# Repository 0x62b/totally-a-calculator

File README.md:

# totally a calculator
This is a RPi Pico powered...calculator...with an extensive library of..."extra apps" one could say.
The sole purpose of this project is to satisfy the ask of one of my classmates :sob:

[Onshape link](https://cad.onshape.com/documents/416f156d5c7fec03dfea0d3a/w/a37f3b67ee07a3cc1823a5f4/e/b4b6719643a130719caaa4b0)
Note: the display appears to be unaligned due to the fact that i used a different display to the model in the render. However, I designed the case around the display being used, so it should be fine.

## Repo structure
`firmware/` for the (not completed) firmware
`cad/` for CAD design files
`images/` for images in this readme
`pcb/` for KiCad design files and `pcb/gerbers` for production files
`bom.csv` for BOM

## Cost
The BOM prices are approximate due to conversion rates and Aliexpress fluctuations
BOM: 27.03 USD
PCB: 4 USD + 1.5 USD shipping (approx)
Total: 32.53 USD

## Assembly
Prerequisites: print the case parts and solder the PCB
1. Put PCB into bottom case
2. Screw top case onto bottom case
3. Glue or otherwise stick each individual keycap onto the buttons
4. Attach the OLED
5. Screw it in
6. Flash the MicroPython firmware for the Pico
7. Upload the python file in `firmware/`
8. yay

## Images

### Schematic
Beautifully clean and organised (/s) schematic

### PCB render

### Full render

### Zine

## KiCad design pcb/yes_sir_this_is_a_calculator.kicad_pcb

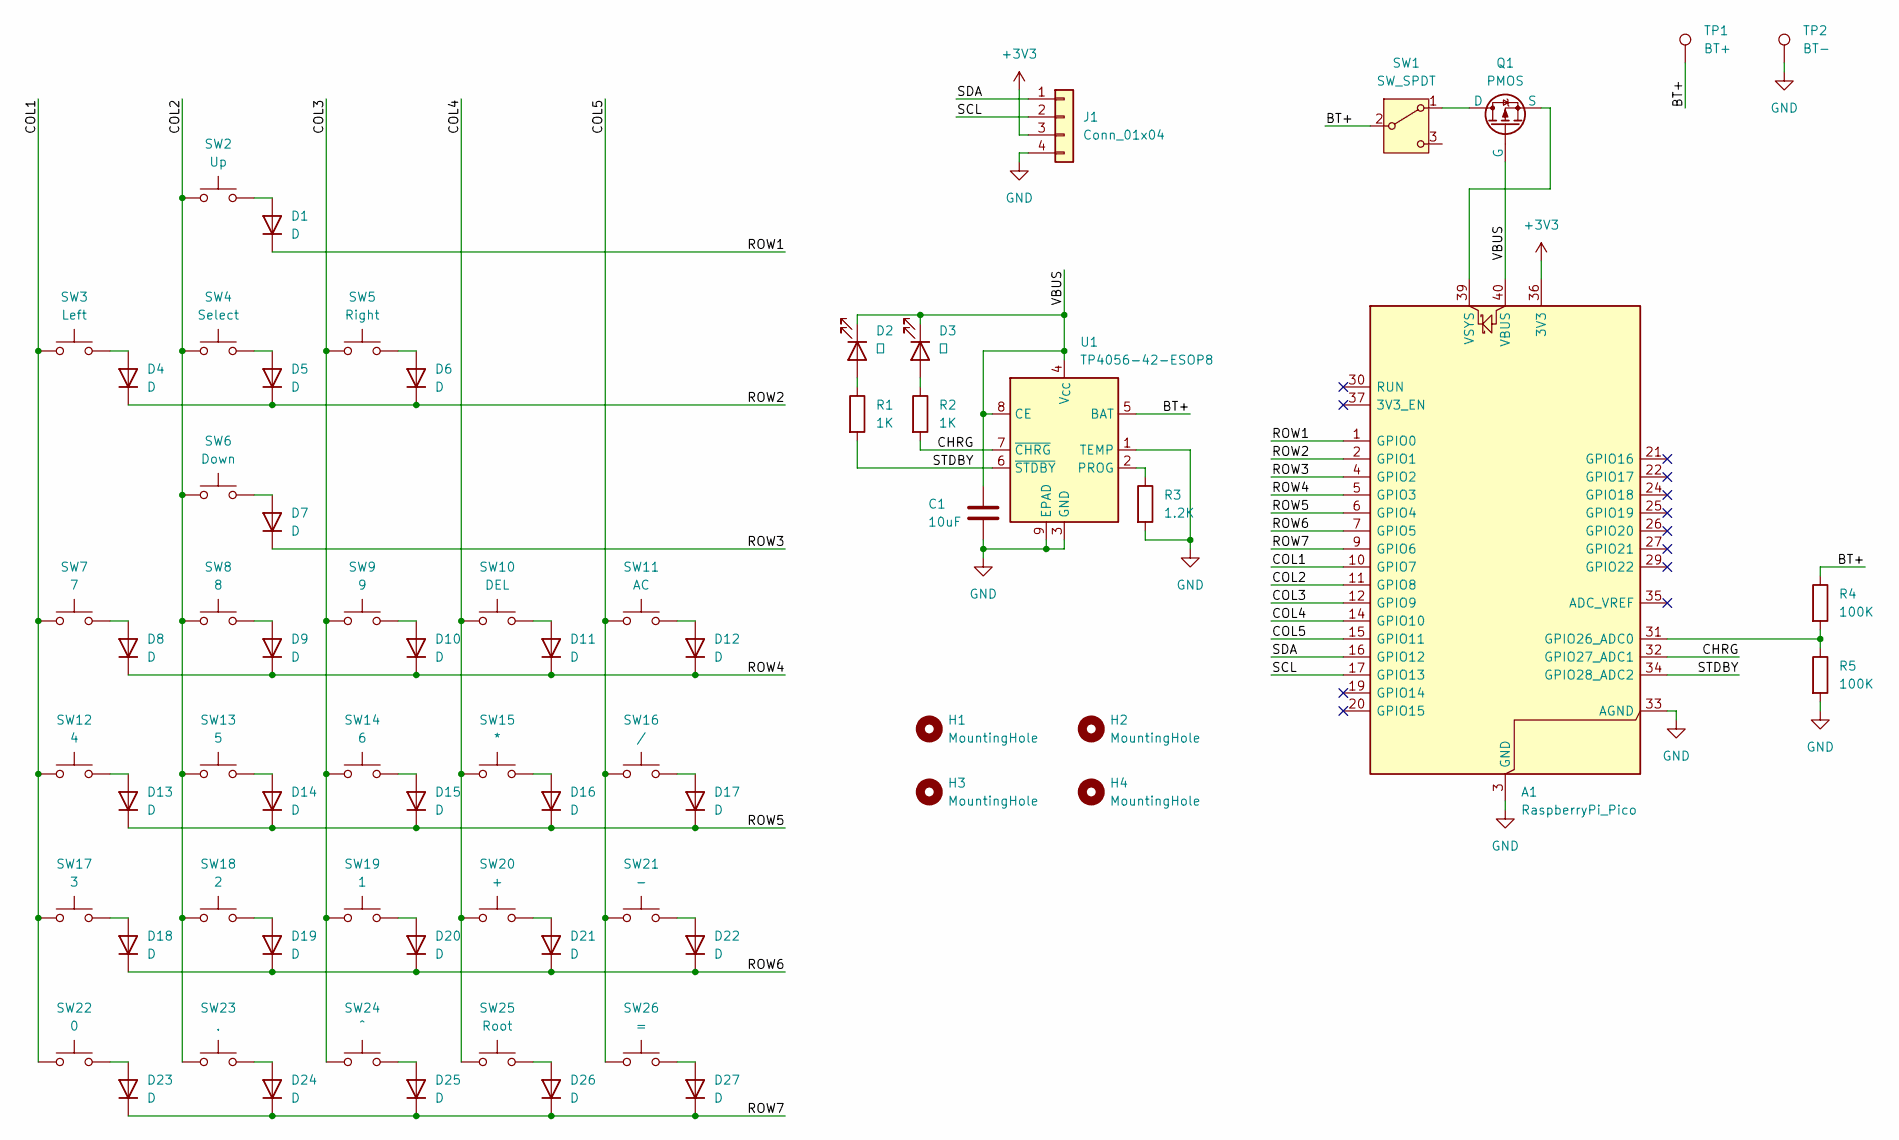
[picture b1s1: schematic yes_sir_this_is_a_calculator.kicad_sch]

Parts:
A1: RaspberryPi_Pico; RaspberryPi_Pico_Common_Unspecified
C1: 10uF; C_0402_1005Metric
D1, D4, D5, D6, D7, D8, D9, D10, D11, D12, D13, D14, D15, D16, D17, D18, D19, D20, D21, D22, D23, D24, D25, D26, D27: D; D_SOD-123
D2: 绿; LED_0402_1005Metric
D3: 红; LED_0402_1005Metric
H1, H2, H3, H4: MountingHole; MountingHole_2.2mm_M2
J1: Conn_01x04; PinSocket_1x04_P2.54mm_Vertical
Q1: PMOS; SOT-23
R1, R2: 1K; R_0402_1005Metric
R3: 1.2K; R_0402_1005Metric
R4, R5: 100K; R_0402_1005Metric
SW1: SW_SPDT; SW_SPDT_PCM12
SW2: Up; SW_PUSH_6mm
SW3: Left; SW_PUSH_6mm
SW4: Select; SW_PUSH_6mm
SW5: Right; SW_PUSH_6mm
SW6: Down; SW_PUSH_6mm
SW7: 7; SW_PUSH_6mm
SW8: 8; SW_PUSH_6mm
SW9: 9; SW_PUSH_6mm
SW10: DEL; SW_PUSH_6mm
SW11: AC; SW_PUSH_6mm
SW12: 4; SW_PUSH_6mm
SW13: 5; SW_PUSH_6mm
SW14: 6; SW_PUSH_6mm
SW15: *; SW_PUSH_6mm
SW16: /; SW_PUSH_6mm
SW17: 3; SW_PUSH_6mm
SW18: 2; SW_PUSH_6mm
SW19: 1; SW_PUSH_6mm
SW20: +; SW_PUSH_6mm
SW21: -; SW_PUSH_6mm
SW22: 0; SW_PUSH_6mm
SW23: .; SW_PUSH_6mm
SW24: ^; SW_PUSH_6mm
SW25: Root; SW_PUSH_6mm
SW26: =; SW_PUSH_6mm
TP1: BT+; TestPoint_Pad_D3.0mm
TP2: BT-; TestPoint_Pad_D3.0mm
U1: TP4056-42-ESOP8; SOIC-8-1EP_3.9x4.9mm_P1.27mm_EP2.41x3.3mm_ThermalVias

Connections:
+3V3: A1.36 (3V3), J1.3
/BT+: R4.1, SW1.2 (B), TP1.1, U1.5 (BAT)
/CHRG: A1.32 (GPIO27_ADC1), R2.2, U1.7 (~CHRG)
/COL1: A1.10 (GPIO7), SW3.1, SW7.1, SW12.1, SW17.1, SW22.1
/COL2: A1.11 (GPIO8), SW2.1, SW4.1, SW6.1, SW8.1, SW13.1, SW18.1, SW23.1
/COL3: A1.12 (GPIO9), SW5.1, SW9.1, SW14.1, SW19.1, SW24.1
/COL4: A1.14 (GPIO10), SW10.1, SW15.1, SW20.1, SW25.1
/COL5: A1.15 (GPIO11), SW11.1, SW16.1, SW21.1, SW26.1
/ROW1: A1.1 (GPIO0), D1.1 (K)
/ROW2: A1.2 (GPIO1), D4.1 (K), D5.1 (K), D6.1 (K)
/ROW3: A1.4 (GPIO2), D7.1 (K)
/ROW4: A1.5 (GPIO3), D8.1 (K), D9.1 (K), D10.1 (K), D11.1 (K), D12.1 (K)
/ROW5: A1.6 (GPIO4), D13.1 (K), D14.1 (K), D15.1 (K), D16.1 (K), D17.1 (K)
/ROW6: A1.7 (GPIO5), D18.1 (K), D19.1 (K), D20.1 (K), D21.1 (K), D22.1 (K)
/ROW7: A1.9 (GPIO6), D23.1 (K), D24.1 (K), D25.1 (K), D26.1 (K), D27.1 (K)
/SCL: A1.17 (GPIO13), J1.2
/SDA: A1.16 (GPIO12), J1.1
/STDBY: A1.34 (GPIO28_ADC2), R1.2, U1.6 (~STDBY)
/VBUS: A1.40 (VBUS), C1.2, D2.1 (K), D3.1 (K), Q1.2 (G), U1.4 (V_{CC}), U1.8 (CE)
GND: A1.3 (GND), A1.8 (GND), A1.13 (GND), A1.18 (GND), A1.23 (GND), A1.28 (GND), A1.33 (AGND), A1.38 (GND), C1.1, J1.4, R3.2, R5.2, TP2.1, U1.1 (TEMP), U1.3 (GND), U1.9 (EPAD)
unnamed: A1.31 (GPIO26_ADC0), R4.2, R5.1
unnamed: A1.39 (VSYS), Q1.3 (S)
unnamed: D1.2 (A), SW2.2
unnamed: D2.2 (A), R1.1
unnamed: D3.2 (A), R2.1
unnamed: D4.2 (A), SW3.2
unnamed: D5.2 (A), SW4.2
unnamed: D6.2 (A), SW5.2
unnamed: D7.2 (A), SW6.2
unnamed: D8.2 (A), SW7.2
unnamed: D9.2 (A), SW8.2
unnamed: D10.2 (A), SW9.2
unnamed: D11.2 (A), SW10.2
unnamed: D12.2 (A), SW11.2
unnamed: D13.2 (A), SW12.2
unnamed: D14.2 (A), SW13.2
unnamed: D15.2 (A), SW14.2
unnamed: D16.2 (A), SW15.2
unnamed: D17.2 (A), SW16.2
unnamed: D18.2 (A), SW17.2
unnamed: D19.2 (A), SW18.2
unnamed: D20.2 (A), SW19.2
unnamed: D21.2 (A), SW20.2
unnamed: D22.2 (A), SW21.2
unnamed: D23.2 (A), SW22.2
unnamed: D24.2 (A), SW23.2
unnamed: D25.2 (A), SW24.2
unnamed: D26.2 (A), SW25.2
unnamed: D27.2 (A), SW26.2
unnamed: Q1.1 (D), SW1.1 (A)
unnamed: R3.1, U1.2 (PROG)

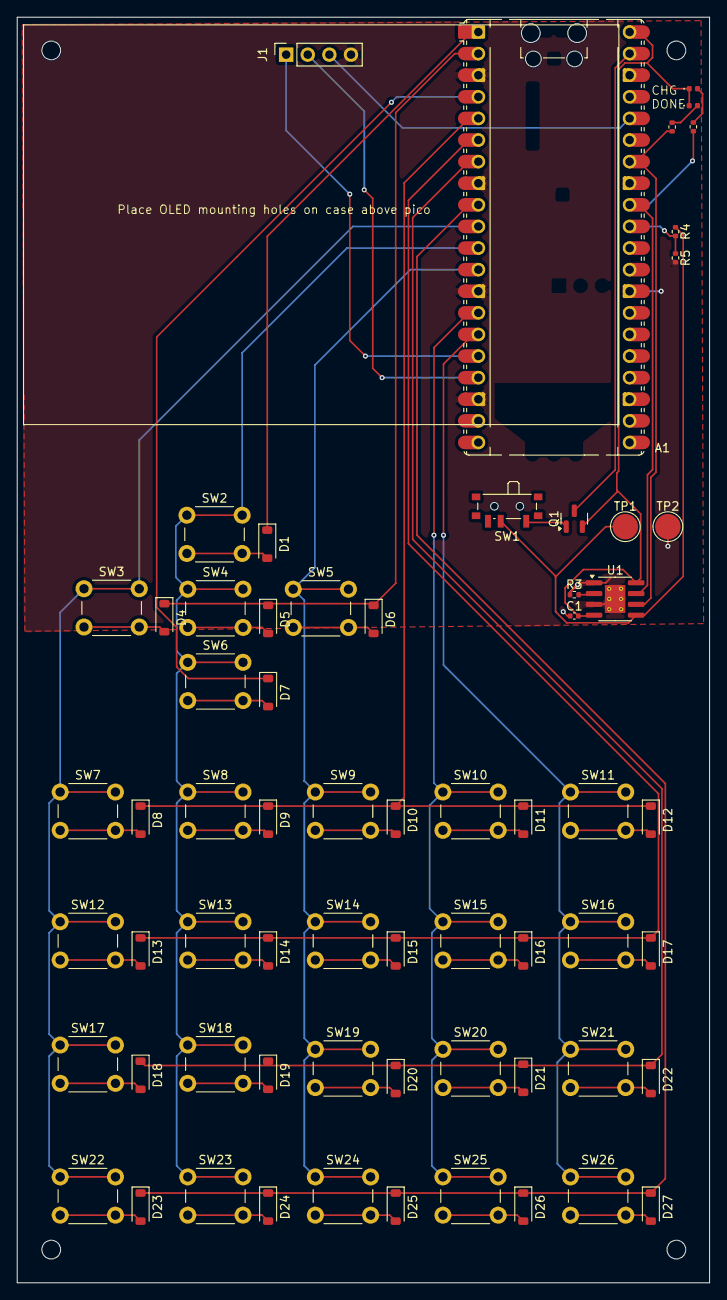
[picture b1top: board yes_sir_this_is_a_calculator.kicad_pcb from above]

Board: 2 copper layers, 81.4 x 148.8 mm, 69 parts (0 on the bottom side), 51 nets.

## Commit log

2026-05-05 stuff
2026-05-05 firmware + gitignore
2026-05-05 CAD files
2026-05-05 add pico to bom
2026-05-28 add gerbers
